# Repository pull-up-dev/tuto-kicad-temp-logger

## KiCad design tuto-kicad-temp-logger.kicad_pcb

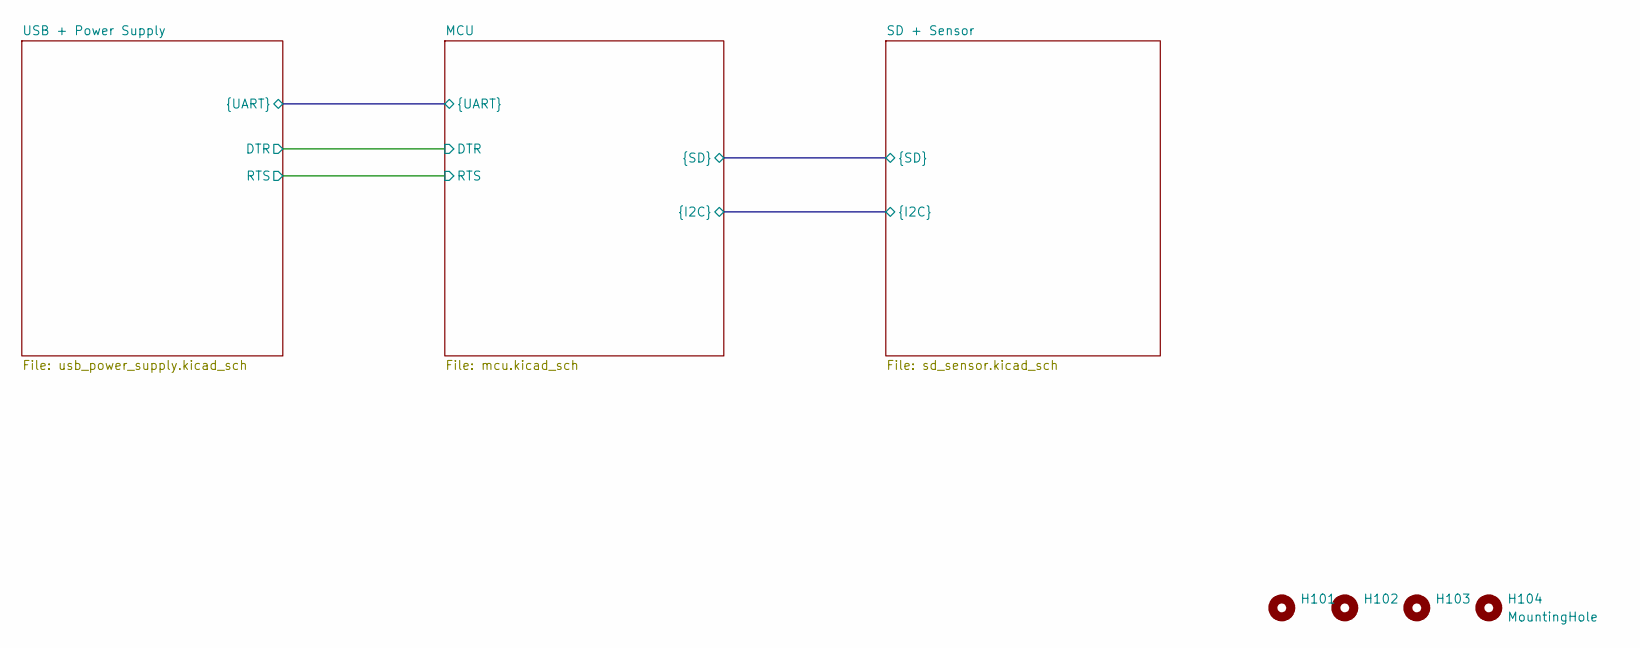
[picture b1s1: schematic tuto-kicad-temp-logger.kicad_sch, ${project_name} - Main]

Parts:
H101, H102, H103, H104: MountingHole; MountingHole_4.3mm_M4

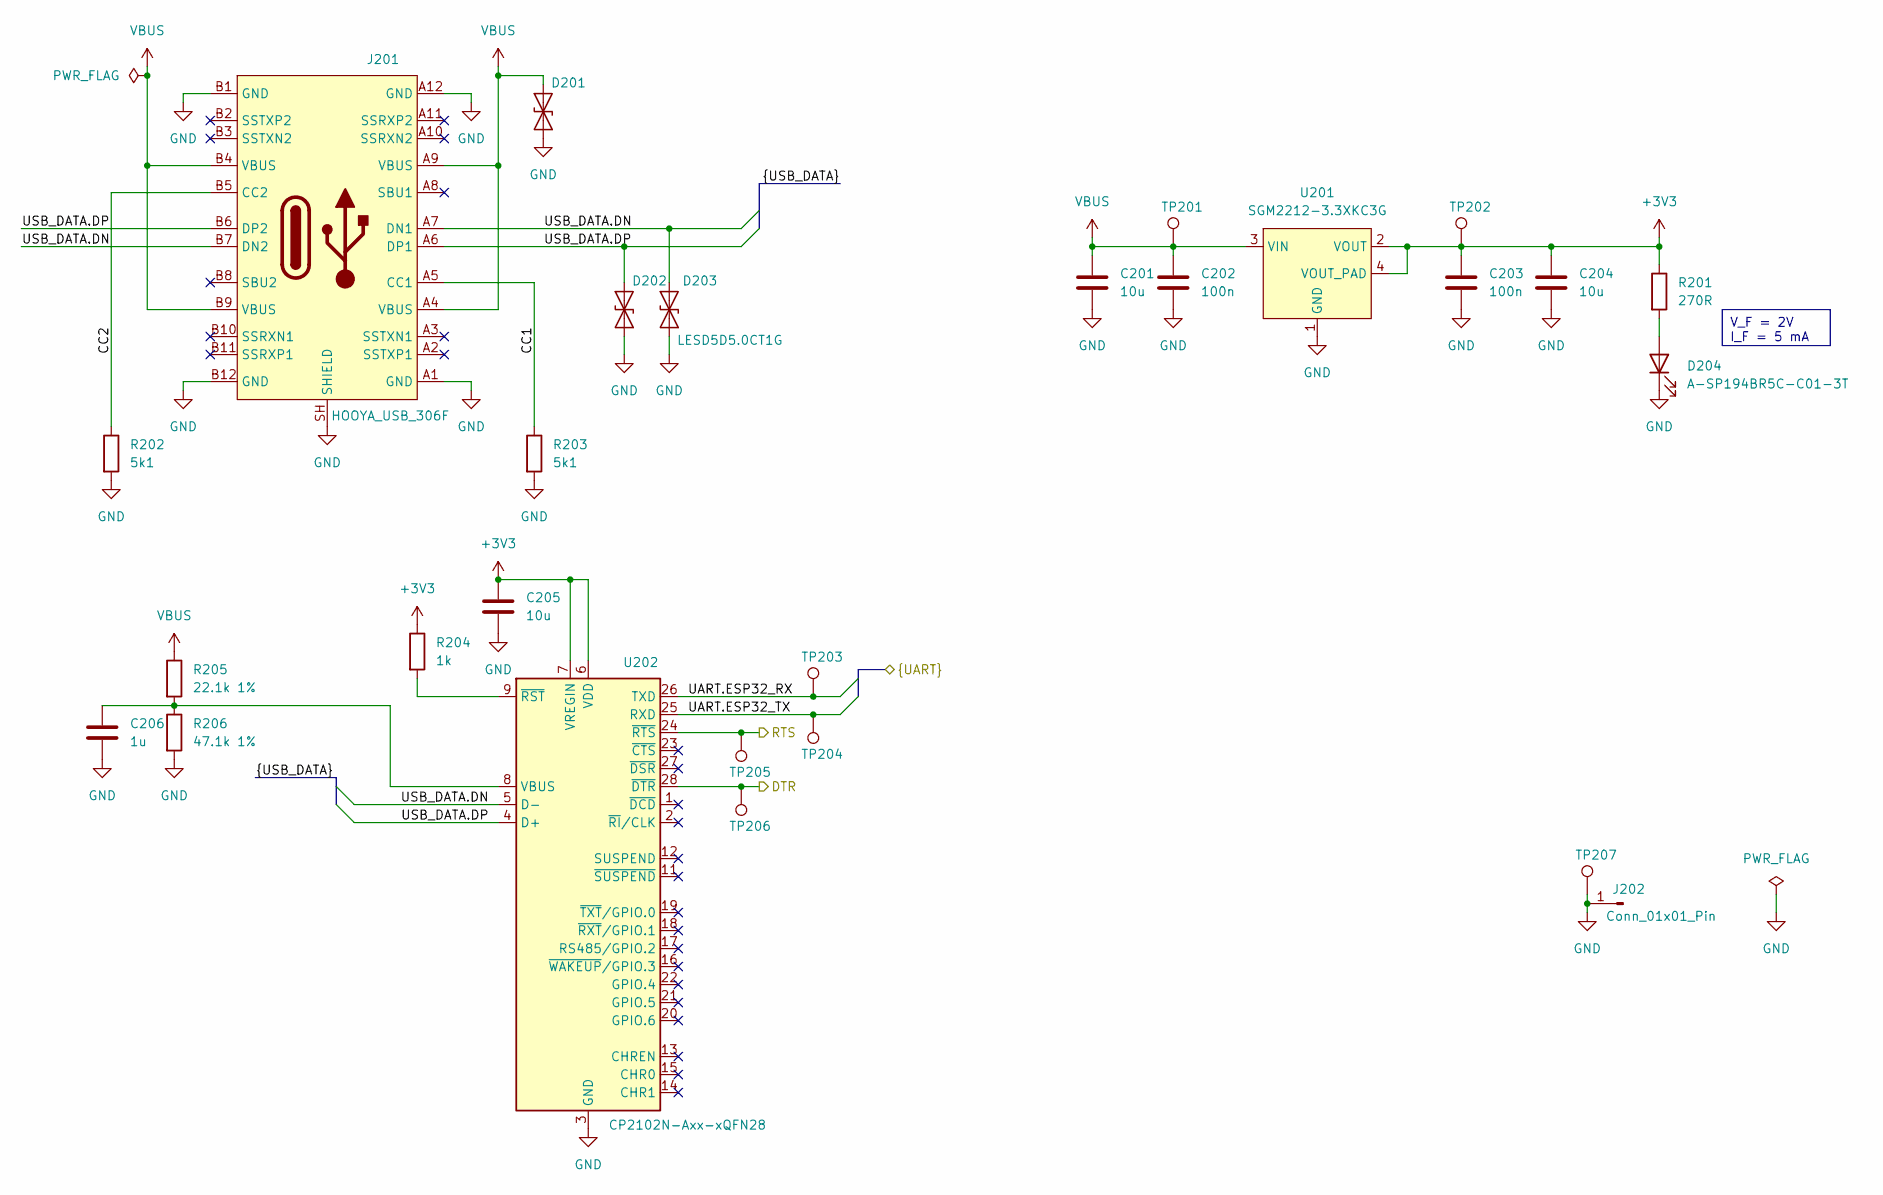
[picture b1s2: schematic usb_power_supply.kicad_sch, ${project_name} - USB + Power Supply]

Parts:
C201, C204, C205: 10u; C_0402_1005Metric
C202, C203: 100n; C_0402_1005Metric
C206: 1u; C_0402_1005Metric
D201, D202, D203: LESD5D5.0CT1G; D_SOD-523_non-pol
D204: A-SP194BR5C-C01-3T; LED_0603_1608Metric
J201: HOOYA_USB_306F
J202: Conn_01x01_Pin; PinHeader_1x01_P2.54mm_Vertical
R201: 270R; R_0402_1005Metric
R202, R203: 5k1; R_0402_1005Metric
R204: 1k; R_0402_1005Metric
R205: 22.1k 1%; R_0402_1005Metric
R206: 47.1k 1%; R_0402_1005Metric
TP201, TP202, TP203, TP204, TP205, TP206, TP207: TestPoint; TestPoint_Pad_D2.0mm
U201: SGM2212-3.3XKC3G; SOT-223
U202: CP2102N-Axx-xQFN28; QFN-28-1EP_5x5mm_P0.5mm_EP3.35x3.35mm

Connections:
+3V3: C203.1, C204.1, C205.1, R201.1, R204.1, TP202.1, U201.2 (VOUT), U201.4 (VOUT_PAD), U202.6 (VDD), U202.7 (VREGIN); also elsewhere on the board
/MCU/DTR: TP206.1, U202.28 (~DTR); also elsewhere on the board
/MCU/RTS: TP205.1, U202.24 (~RTS); also elsewhere on the board
/MCU/UART.ESP32_RX: TP203.1, U202.26 (TXD); also elsewhere on the board
/MCU/UART.ESP32_TX: TP204.1, U202.25 (RXD); also elsewhere on the board
/USB + Power Supply/CC1: J201.A5 (CC1), R203.1
/USB + Power Supply/CC2: J201.B5 (CC2), R202.1
/USB + Power Supply/USB_DATA.DN: D203.2 (A2), J201.A7 (DN1), J201.B7 (DN2), U202.5 (D-)
/USB + Power Supply/USB_DATA.DP: D202.2 (A2), J201.A6 (DP1), J201.B6 (DP2), U202.4 (D+)
GND: C201.2, C202.2, C203.2, C204.2, C205.2, C206.2, D201.1 (A1), D202.1 (A1), D203.1 (A1), D204.1 (K), J201.A1 (GND), J201.A12 (GND), J201.B1 (GND), J201.B12 (GND), J201.SH (SHIELD), J202.1, R202.2, R203.2, R206.2, TP207.1, U201.1 (GND), U202.3 (GND), U202.29 (GND); also elsewhere on the board
unnamed: D204.2 (A), R201.2
unnamed: C206.1, R205.2, R206.1, U202.8 (VBUS)
unnamed: R204.2, U202.9 (~RST)
VBUS: C201.1, C202.1, D201.2 (A2), J201.A4 (VBUS), J201.A9 (VBUS), J201.B4 (VBUS), J201.B9 (VBUS), R205.1, TP201.1, U201.3 (VIN)

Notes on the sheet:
V_F = 2V I_F = 5 mA

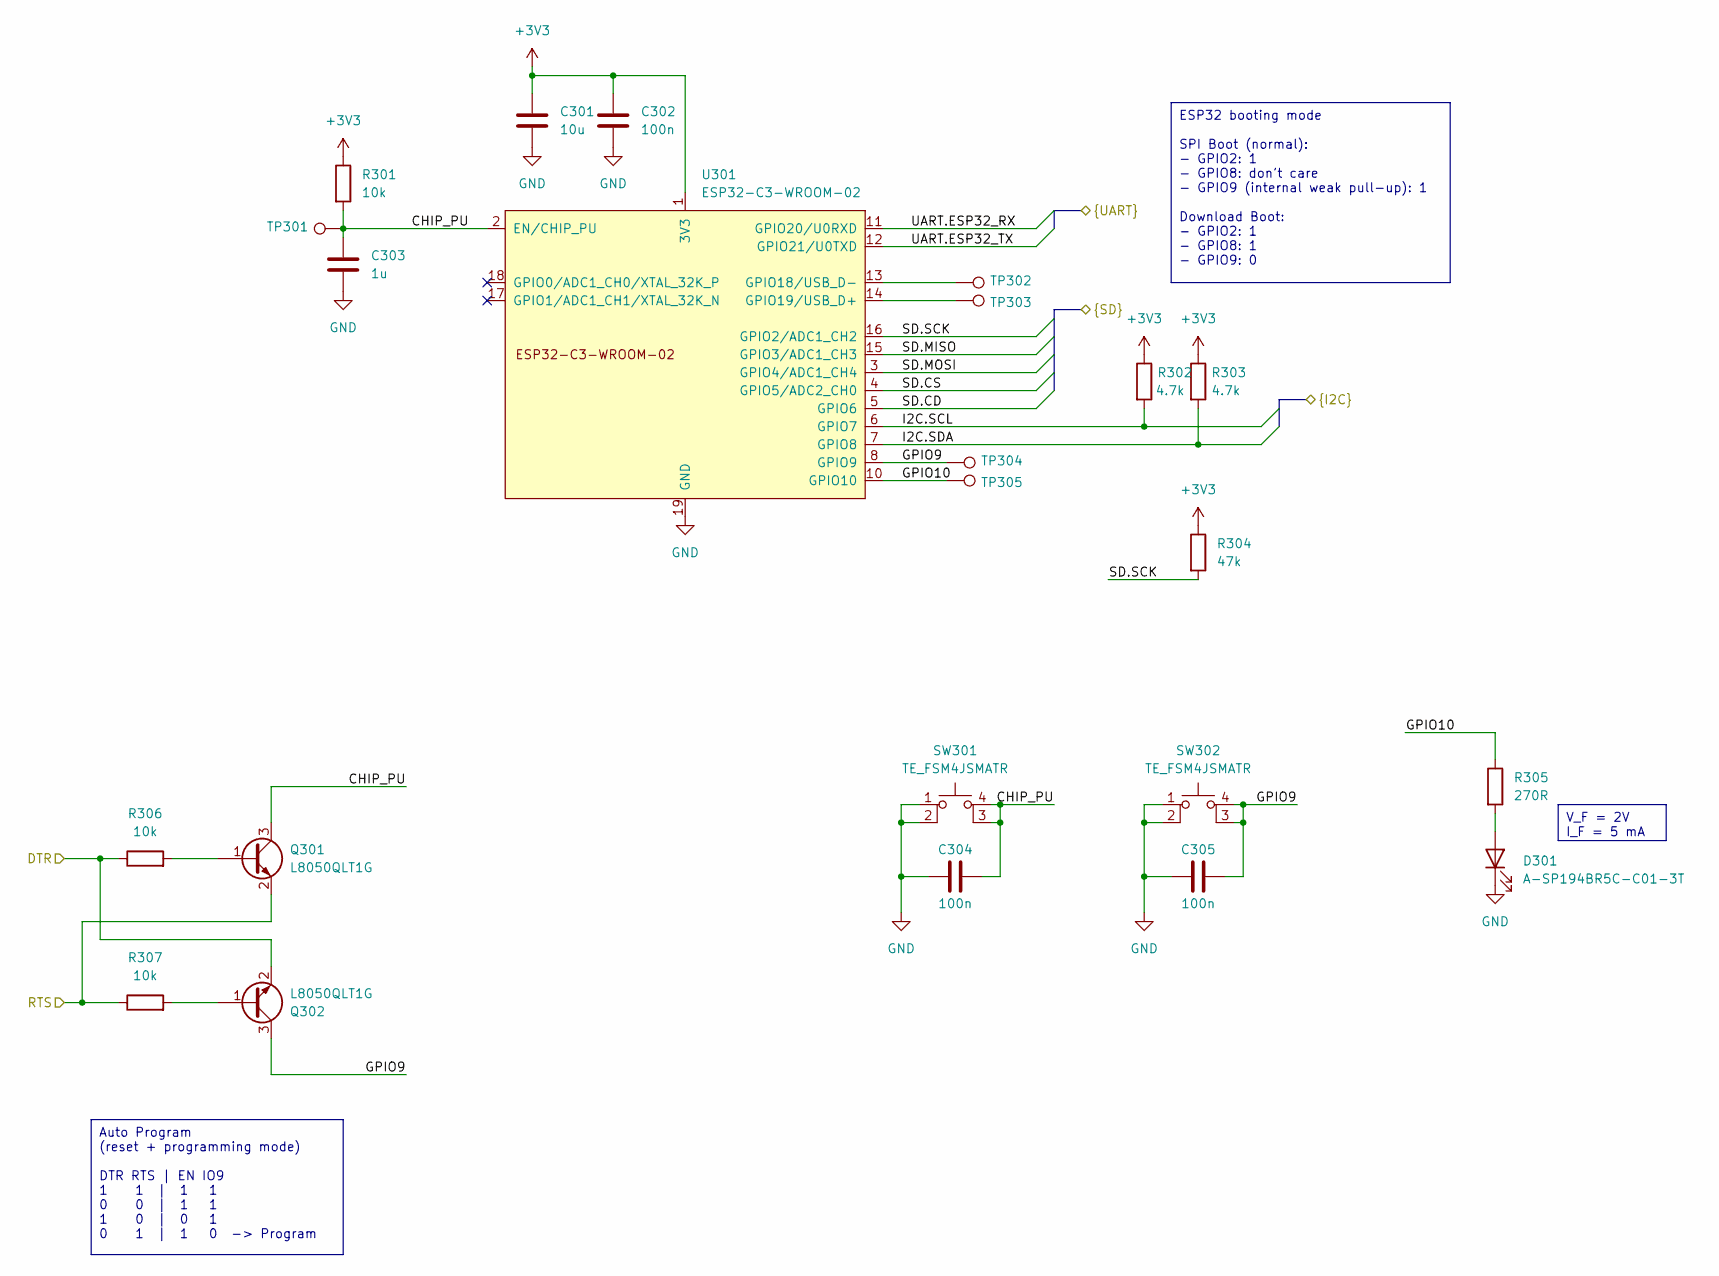
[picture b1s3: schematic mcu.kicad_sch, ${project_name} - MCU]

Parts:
C301: 10u; C_0402_1005Metric
C302, C304, C305: 100n; C_0402_1005Metric
C303: 1u; C_0402_1005Metric
D301: A-SP194BR5C-C01-3T; LED_0603_1608Metric
Q301, Q302: L8050QLT1G; SOT-23
R301, R306, R307: 10k; R_0402_1005Metric
R302, R303: 4.7k; R_0402_1005Metric
R304: 47k; R_0402_1005Metric
R305: 270R; R_0402_1005Metric
SW301, SW302: TE_FSM4JSMATR
TP301, TP302, TP303, TP304, TP305: TestPoint; TestPoint_Pad_D2.0mm
U301: ESP32-C3-WROOM-02

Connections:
+3V3: C301.1, C302.1, R301.1, R302.1, R303.1, R304.1, U301.1 (3V3); also elsewhere on the board
/MCU/CHIP_PU: C303.1, C304.2, Q301.3 (C), R301.2, SW301.3 (K), SW301.4 (A), TP301.1, U301.2 (EN/CHIP_PU)
/MCU/DTR: Q302.2 (E), R306.1; also elsewhere on the board
/MCU/GPIO9: C305.2, Q302.3 (C), SW302.3 (K), SW302.4 (A), TP304.1, U301.8 (GPIO9)
/MCU/GPIO10: R305.1, TP305.1, U301.10 (GPIO10)
/MCU/I2C.SCL: R302.2, U301.6 (GPIO7); also elsewhere on the board
/MCU/I2C.SDA: R303.2, U301.7 (GPIO8); also elsewhere on the board
/MCU/RTS: Q301.2 (E), R307.1; also elsewhere on the board
/MCU/SD.CD: U301.5 (GPIO6); also elsewhere on the board
/MCU/SD.CS: U301.4 (GPIO5/ADC2_CH0); also elsewhere on the board
/MCU/SD.MISO: U301.15 (GPIO3/ADC1_CH3); also elsewhere on the board
/MCU/SD.MOSI: U301.3 (GPIO4/ADC1_CH4); also elsewhere on the board
/MCU/SD.SCK: R304.2, U301.16 (GPIO2/ADC1_CH2); also elsewhere on the board
/MCU/UART.ESP32_RX: U301.11 (GPIO20/U0RXD); also elsewhere on the board
/MCU/UART.ESP32_TX: U301.12 (GPIO21/U0TXD); also elsewhere on the board
GND: C301.2, C302.2, C303.2, C304.1, C305.1, D301.1 (K), SW301.1, SW301.2, SW302.1, SW302.2, U301.9 (GND), U301.19 (GND); also elsewhere on the board
unnamed: D301.2 (A), R305.2
unnamed: Q301.1 (B), R306.2
unnamed: Q302.1 (B), R307.2
unnamed: TP302.1, U301.13 (GPIO18/USB_D-)
unnamed: TP303.1, U301.14 (GPIO19/USB_D+)

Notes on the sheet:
V_F = 2V I_F = 5 mA
ESP32 booting mode SPI Boot (normal): - GPIO2: 1 - GPIO8: don't care - GPIO9 (internal weak pull-up): 1 Download Boot: - GPIO2: 1 - GPIO8: 1 - GPIO9: 0
Auto Program (reset + programming mode) DTR RTS | EN IO9 1 1 | 1 1 0 0 | 1 1 1 0 | 0 1 0 1 | 1 0 -> Program

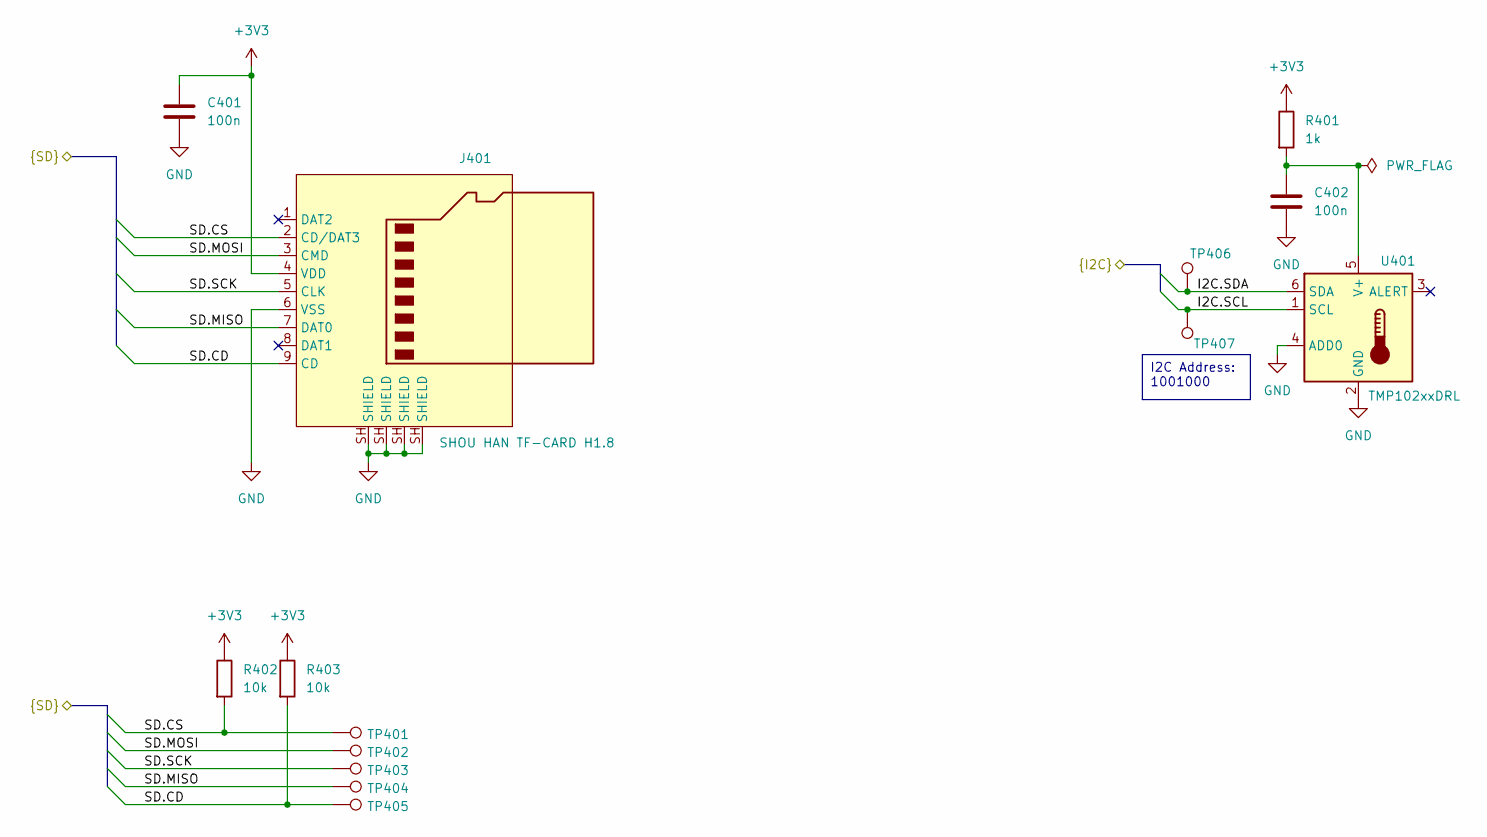
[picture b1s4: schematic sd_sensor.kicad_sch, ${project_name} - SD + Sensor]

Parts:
C401, C402: 100n; C_0402_1005Metric
J401: SHOU HAN TF-CARD H1.8; SHOUHAN_TF_CARD_H1.8
R401: 1k; R_0402_1005Metric
R402, R403: 10k; R_0402_1005Metric
TP401, TP402, TP403, TP404, TP405, TP406, TP407: TestPoint; TestPoint_Pad_D2.0mm
U401: TMP102xxDRL; SOT-563

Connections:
+3V3: C401.1, J401.4 (VDD), R401.1, R402.1, R403.1; also elsewhere on the board
/MCU/I2C.SCL: TP407.1, U401.1 (SCL); also elsewhere on the board
/MCU/I2C.SDA: TP406.1, U401.6 (SDA); also elsewhere on the board
/MCU/SD.CD: J401.9 (CD), R403.2, TP405.1; also elsewhere on the board
/MCU/SD.CS: J401.2 (CD/DAT3), R402.2, TP401.1; also elsewhere on the board
/MCU/SD.MISO: J401.7 (DAT0), TP404.1; also elsewhere on the board
/MCU/SD.MOSI: J401.3 (CMD), TP402.1; also elsewhere on the board
/MCU/SD.SCK: J401.5 (CLK), TP403.1; also elsewhere on the board
GND: C401.2, C402.2, J401.6 (VSS), J401.SH (SHIELD), U401.2 (GND), U401.4 (ADD0); also elsewhere on the board
unnamed: C402.1, R401.2, U401.5 (V+)

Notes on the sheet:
I2C Address: 1001000

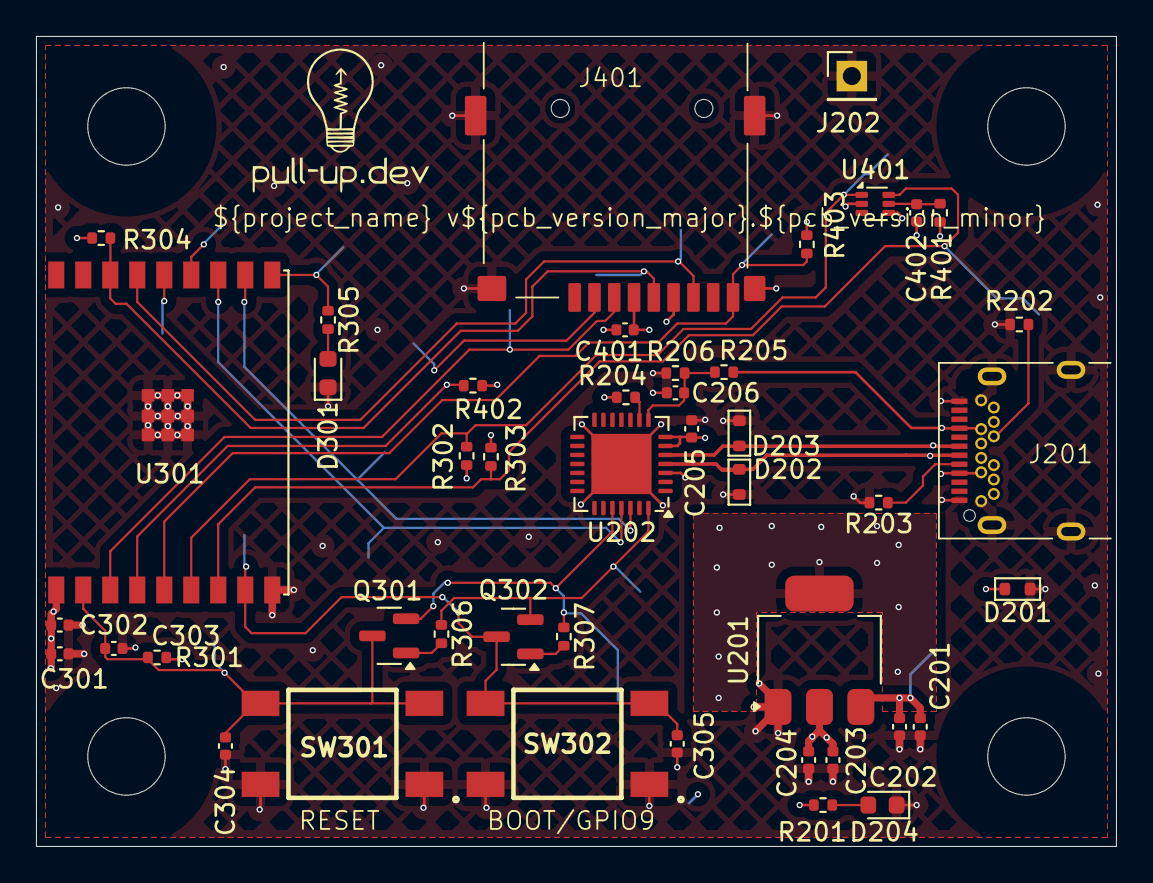
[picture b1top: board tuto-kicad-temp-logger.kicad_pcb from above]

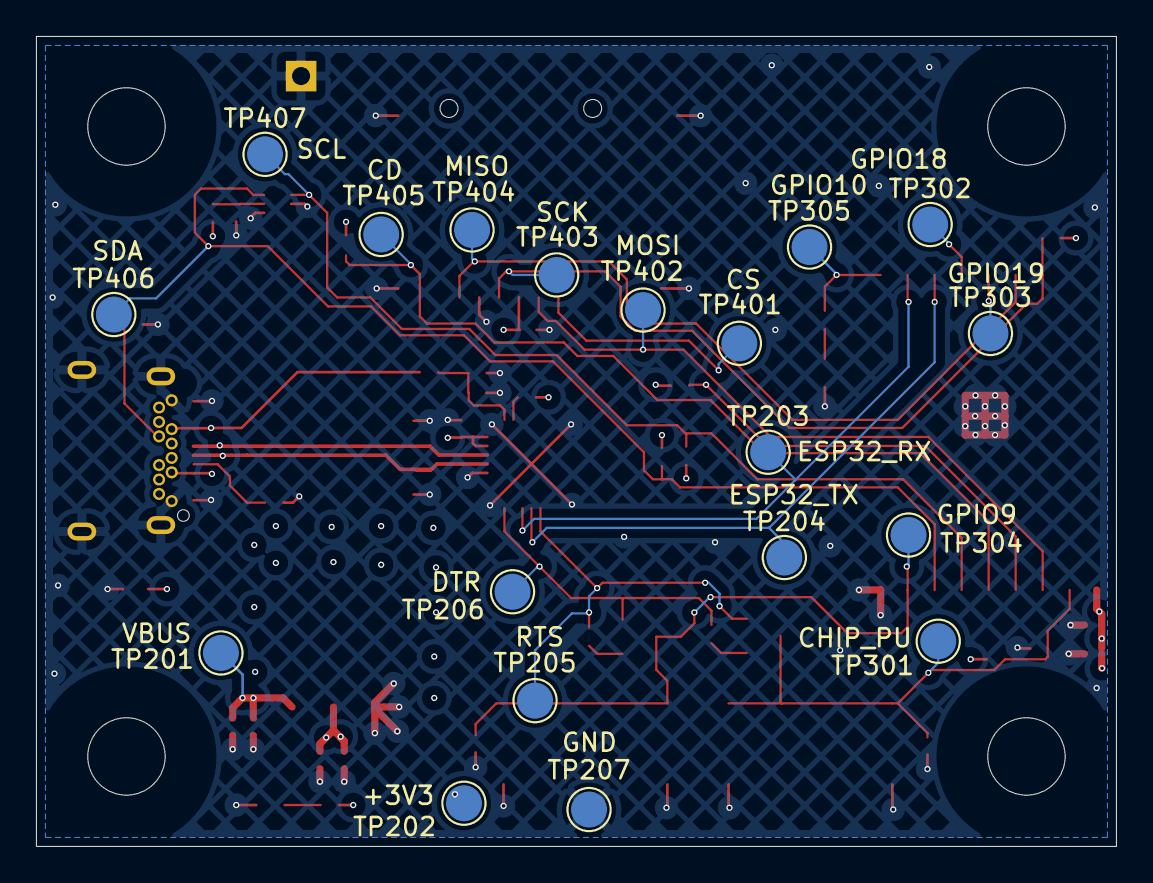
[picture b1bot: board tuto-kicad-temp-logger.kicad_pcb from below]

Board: 4 copper layers, 60.0 x 45.0 mm, 68 parts (19 on the bottom side), 30 nets.

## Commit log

2024-07-07 Création du projet, ajout des pages, configuration
2024-07-07 Création des libraries de symboles et d'empreintes
2024-07-08 Ajouter composant LESD5D5.0CT1G (diode ESD)
2024-07-09 Ajouter composants: transistor NPN, régulateur de tension
2024-07-13 Ajouter composant: support de carte SD
2024-08-03 Ajouter composants du connecteur USB-C et bouton poussoir
2024-08-05 Ajout des composants et connexion page "USB + Power supply"
2024-08-10 Ajouter des composants + connexion page "MCU"
2024-08-10 Ajout des composants + connexion page "SD + Sensor"
2024-08-10 Connexion des pages du schéma
2024-08-10 Vérification des règles électriques
2024-08-10 Configuration du layout
2024-08-11 Placement des composants
2024-08-12 Correction précoce d'erreurs de DRC: ajout de règles utilisateur
2024-08-17 Routage
2024-08-17 Ajout de plans hachurés au top et bottom
2024-08-18 Ajout des annotations
2024-08-25 Silkscreen, DRC et corrections
2024-08-25 Placement de la référence
